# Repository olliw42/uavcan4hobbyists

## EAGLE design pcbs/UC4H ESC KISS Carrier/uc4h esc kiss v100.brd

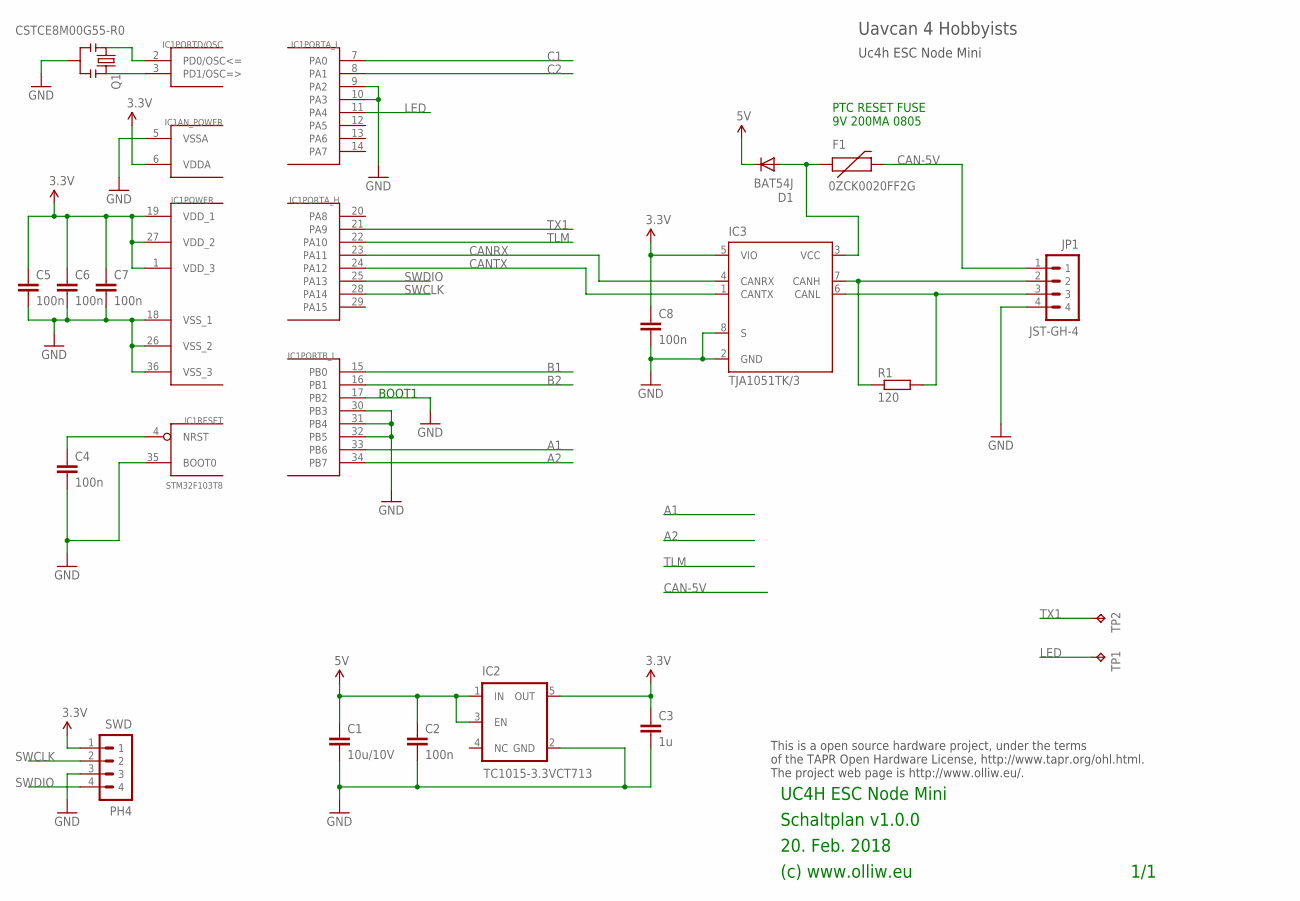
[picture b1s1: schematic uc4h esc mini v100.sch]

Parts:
C1: 10u/10V; C1206
C2, C4, C5, C6, C7, C8: 100n; C0603K
C3: 1u; C0603K
D1: BAT54J; SOD110-R
F1: 0ZCK0020FF2G; FUSE-0805
IC1: STM32F103T8; VFQFPN36
IC2: TC1015-3.3VCT713; SOT23-5
IC3: TJA1051TK/3; HVSON8
JP1: JST-GH-4; SM04B-GHS-TB
Q1: CSTCE8M00G55-R0; RESONATOR-SMD
R1: 120; R0603
SWD: PH4; 4X1_1P27_OCT_BILEX
TP1, TP2: TPB1,27; B1,27

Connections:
3.3V: C3.1, C5.1, C6.1, C7.1, C8.1, IC1.1 (VDD_3), IC1.6 (VDDA), IC1.19 (VDD_1), IC1.27 (VDD_2), IC2.5 (OUT), IC3.5 (VIO), SWD.1
5V: C1.1, C2.1, D1.C, IC2.1 (IN), IC2.3 (EN); also elsewhere on the board
A1: IC1.33 (PB6)
A2: IC1.34 (PB7)
B1: IC1.15 (PB0)
B2: IC1.16 (PB1)
C1: IC1.7 (PA0)
C2: IC1.8 (PA1)
CAN-5V: F1.2, JP1.1
CANH: IC3.7 (CANH), JP1.2, R1.1
CANL: IC3.6 (CANL), JP1.3, R1.2
CANRX: IC1.23 (PA11), IC3.4 (CANRX)
CANTX: IC1.24 (PA12), IC3.1 (CANTX)
GND: C1.2, C2.2, C3.2, C4.2, C5.2, C6.2, C7.2, C8.2, IC1.5 (VSSA), IC1.9 (PA2), IC1.10 (PA3), IC1.17 (PB2), IC1.18 (VSS_1), IC1.26 (VSS_2), IC1.30 (PB3), IC1.31 (PB4), IC1.32 (PB5), IC1.35 (BOOT0), IC1.36 (VSS_3), IC2.2 (GND), IC3.2 (GND), IC3.8 (S), JP1.4, Q1.2, SWD.3
LED: IC1.11 (PA4), TP1.TP
unnamed: C4.1, IC1.4 (NRST)
unnamed: D1.A, F1.1, IC3.3 (VCC)
unnamed: IC1.2 (PD0/OSC<=), Q1.1
unnamed: IC1.3 (PD1/OSC=>), Q1.3
SWCLK: IC1.28 (PA14), SWD.2
SWDIO: IC1.25 (PA13), SWD.4
TLM: IC1.22 (PA10)
TX1: IC1.21 (PA9), TP2.TP

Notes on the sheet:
20. Feb. 2018
(c) www.olliw.eu
UC4H ESC Node Mini
Schaltplan v1.0.0
This is a open source hardware project, under the terms of the TAPR Open Hardware License, http://www.tapr.org/ohl.html. The project web page is http://www.olliw.eu/.
1/1
Uc4h ESC Node Mini
Uavcan 4 Hobbyists
BOOT1
PTC RESET FUSE 9V 200MA 0805

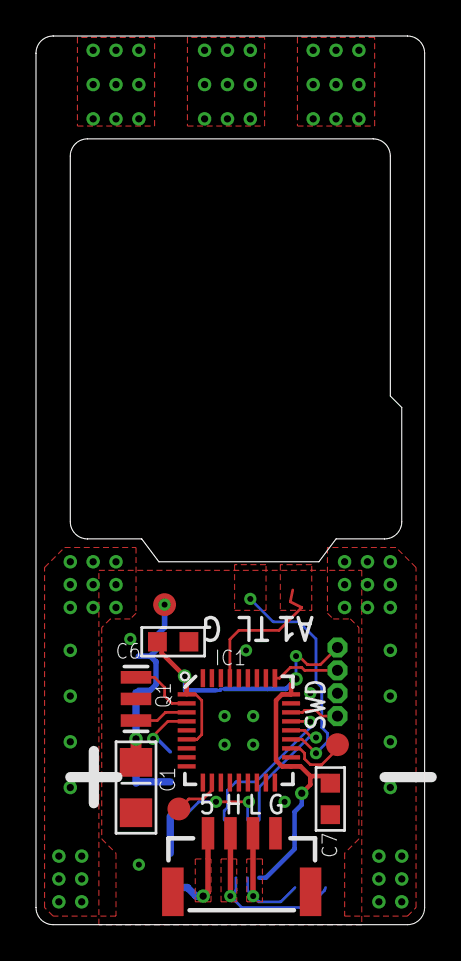
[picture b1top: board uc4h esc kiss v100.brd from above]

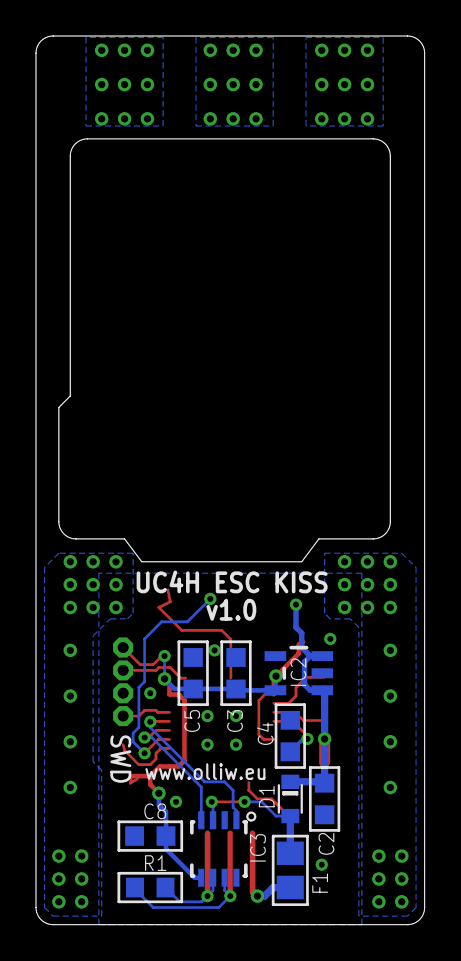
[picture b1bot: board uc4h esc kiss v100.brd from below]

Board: 2 copper layers, 21.6 x 49.4 mm, 20 parts (10 on the bottom side), 16 nets.

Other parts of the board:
TP3: TPB1,27; B1,27

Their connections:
5V: TP3.TP; also elsewhere on the board

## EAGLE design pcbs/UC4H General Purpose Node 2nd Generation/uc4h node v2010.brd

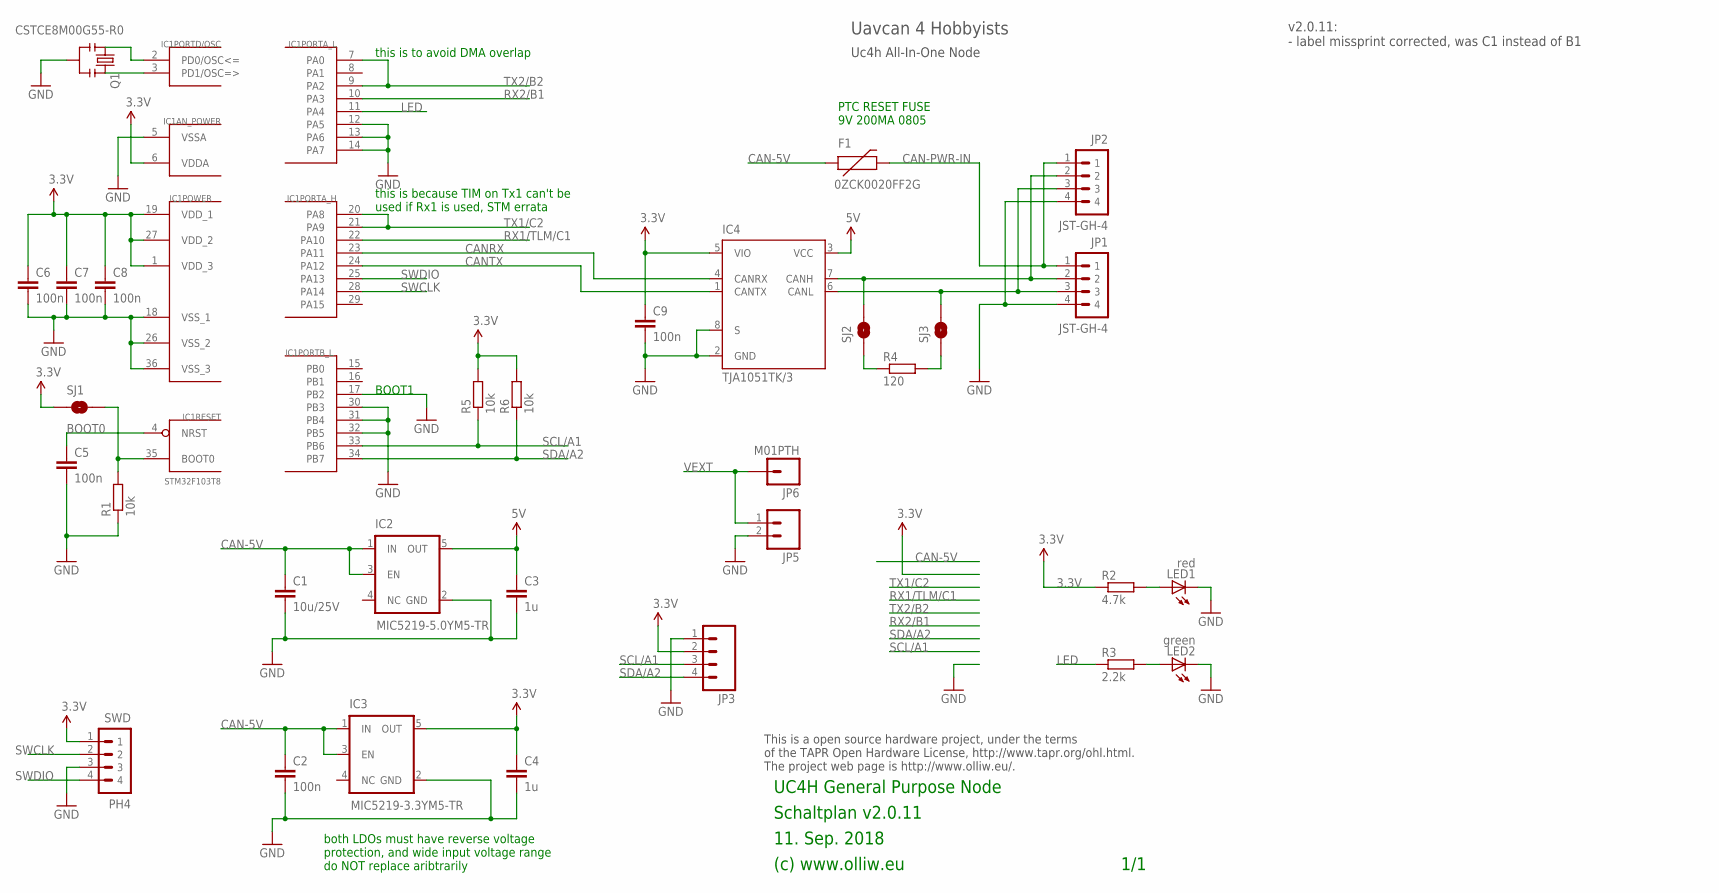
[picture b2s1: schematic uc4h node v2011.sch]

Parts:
C1: 10u/25V; C1206
C2, C5, C6, C7, C8, C9: 100n; C0603K
C3, C4: 1u; C0603K
F1: 0ZCK0020FF2G; FUSE-0805
IC1: STM32F103T8; VFQFPN36
IC2: MIC5219-5.0YM5-TR; SOT23-5
IC3: MIC5219-3.3YM5-TR; SOT23-5
IC4: TJA1051TK/3; HVSON8
JP1, JP2: JST-GH-4; SM04B-GHS-TB
JP3: M04PTH; 1X04
JP5: M02PTH; 1X02
JP6: M01PTH; 1X01
LED1: red; CHIPLED_0603
LED2: green; CHIPLED_0603
Q1: CSTCE8M00G55-R0; RESONATOR-SMD
R1, R5, R6: 10k; R0603
R2: 4.7k; R0603
R3: 2.2k; R0603
R4: 120; R0603
SJ1: BOOT0; SJ_2S-NO
SJ2, SJ3: SOLDERJUMPERNO; SJ_2S-NO
SWD: PH4; 4X1_1P27_OCT_BILEX

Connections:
3.3V: C4.1, C6.1, C7.1, C8.1, C9.1, IC1.1 (VDD_3), IC1.6 (VDDA), IC1.19 (VDD_1), IC1.27 (VDD_2), IC3.5 (OUT), IC4.5 (VIO), JP3.2, R2.1, R5.2, R6.2, SJ1.1, SWD.1
5V: C3.1, IC2.5 (OUT), IC4.3 (VCC)
CAN-5V: C1.1, C2.1, F1.1, IC2.1 (IN), IC2.3 (EN), IC3.1 (IN), IC3.3 (EN)
CAN-PWR-IN: F1.2, JP1.1, JP2.1
CANH: IC4.7 (CANH), JP1.2, JP2.2, SJ2.2
CANL: IC4.6 (CANL), JP1.3, JP2.3, SJ3.2
CANRX: IC1.23 (PA11), IC4.4 (CANRX)
CANTX: IC1.24 (PA12), IC4.1 (CANTX)
GND: C1.2, C2.2, C3.2, C4.2, C5.2, C6.2, C7.2, C8.2, C9.2, IC1.5 (VSSA), IC1.12 (PA5), IC1.13 (PA6), IC1.14 (PA7), IC1.17 (PB2), IC1.18 (VSS_1), IC1.26 (VSS_2), IC1.30 (PB3), IC1.31 (PB4), IC1.32 (PB5), IC1.36 (VSS_3), IC2.2 (GND), IC3.2 (GND), IC4.2 (GND), IC4.8 (S), JP1.4, JP2.4, JP3.1, JP5.2, LED1.C, LED2.C, Q1.2, R1.1, SWD.3
LED: IC1.11 (PA4), R3.1
unnamed: C5.1, IC1.4 (NRST)
unnamed: LED2.A, R3.2
unnamed: R4.1, SJ2.1
unnamed: IC1.2 (PD0/OSC<=), Q1.1
unnamed: IC1.3 (PD1/OSC=>), Q1.3
unnamed: R4.2, SJ3.1
unnamed: IC1.35 (BOOT0), R1.2, SJ1.2
unnamed: LED1.A, R2.2
RX1/TLM/C1: IC1.22 (PA10)
RX2/B1: IC1.10 (PA3)
SWCLK: IC1.28 (PA14), SWD.2
SWDIO: IC1.25 (PA13), SWD.4
TX1/C2: IC1.20 (PA8), IC1.21 (PA9)
TX2/B2: IC1.7 (PA0), IC1.9 (PA2)
VEXT: JP5.1, JP6.1

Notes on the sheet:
11. Sep. 2018
(c) www.olliw.eu
UC4H General Purpose Node
Schaltplan v2.0.11
This is a open source hardware project, under the terms of the TAPR Open Hardware License, http://www.tapr.org/ohl.html. The project web page is http://www.olliw.eu/.
1/1
Uc4h All-In-One Node
Uavcan 4 Hobbyists
BOOT1
PTC RESET FUSE 9V 200MA 0805
both LDOs must have reverse voltage protection, and wide input voltage range do NOT replace aribtrarily
this is to avoid DMA overlap
this is because TIM on Tx1 can't be used if Rx1 is used, STM errata
v2.0.11: - label missprint corrected, was C1 instead of B1

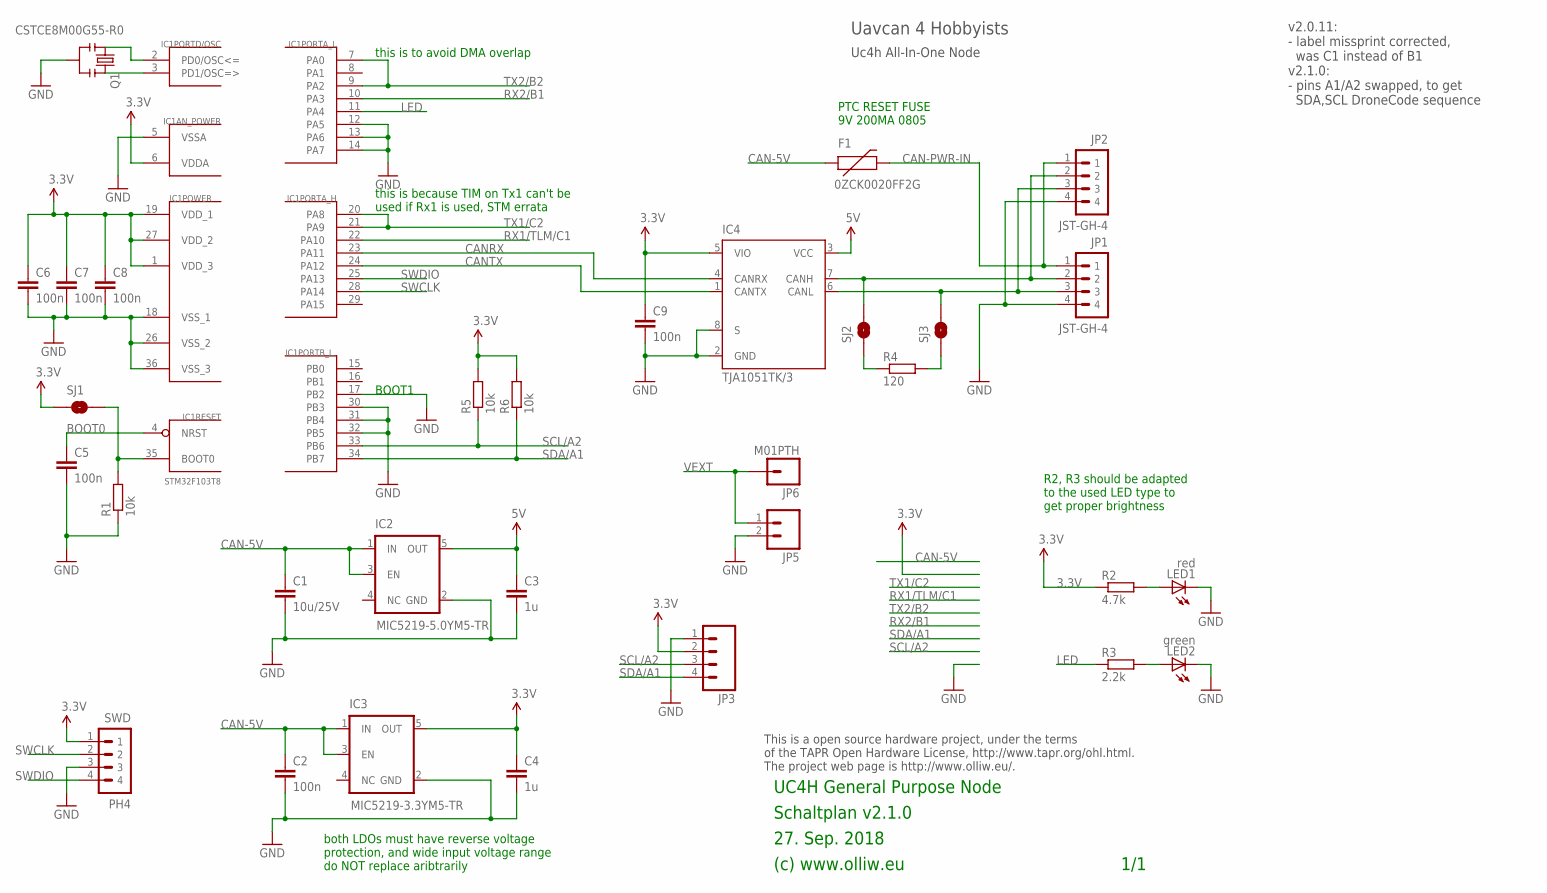
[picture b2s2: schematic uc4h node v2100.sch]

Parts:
C1: 10u/25V; C1206
C2, C5, C6, C7, C8, C9: 100n; C0603K
C3, C4: 1u; C0603K
F1: 0ZCK0020FF2G; FUSE-0805
IC1: STM32F103T8; VFQFPN36
IC2: MIC5219-5.0YM5-TR; SOT23-5
IC3: MIC5219-3.3YM5-TR; SOT23-5
IC4: TJA1051TK/3; HVSON8
JP1, JP2: JST-GH-4; SM04B-GHS-TB
JP3: M04PTH; 1X04
JP5: M02PTH; 1X02
JP6: M01PTH; 1X01
LED1: red; CHIPLED_0603
LED2: green; CHIPLED_0603
Q1: CSTCE8M00G55-R0; RESONATOR-SMD
R1, R5, R6: 10k; R0603
R2: 4.7k; R0603
R3: 2.2k; R0603
R4: 120; R0603
SJ1: BOOT0; SJ_2S-NO
SJ2, SJ3: SOLDERJUMPERNO; SJ_2S-NO
SWD: PH4; 4X1_1P27_OCT_BILEX

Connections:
3.3V: C4.1, C6.1, C7.1, C8.1, C9.1, IC1.1 (VDD_3), IC1.6 (VDDA), IC1.19 (VDD_1), IC1.27 (VDD_2), IC3.5 (OUT), IC4.5 (VIO), JP3.2, R2.1, R5.2, R6.2, SJ1.1, SWD.1
5V: C3.1, IC2.5 (OUT), IC4.3 (VCC)
CAN-5V: C1.1, C2.1, F1.1, IC2.1 (IN), IC2.3 (EN), IC3.1 (IN), IC3.3 (EN)
CAN-PWR-IN: F1.2, JP1.1, JP2.1
CANH: IC4.7 (CANH), JP1.2, JP2.2, SJ2.2
CANL: IC4.6 (CANL), JP1.3, JP2.3, SJ3.2
CANRX: IC1.23 (PA11), IC4.4 (CANRX)
CANTX: IC1.24 (PA12), IC4.1 (CANTX)
GND: C1.2, C2.2, C3.2, C4.2, C5.2, C6.2, C7.2, C8.2, C9.2, IC1.5 (VSSA), IC1.12 (PA5), IC1.13 (PA6), IC1.14 (PA7), IC1.17 (PB2), IC1.18 (VSS_1), IC1.26 (VSS_2), IC1.30 (PB3), IC1.31 (PB4), IC1.32 (PB5), IC1.36 (VSS_3), IC2.2 (GND), IC3.2 (GND), IC4.2 (GND), IC4.8 (S), JP1.4, JP2.4, JP3.1, JP5.2, LED1.C, LED2.C, Q1.2, R1.1, SWD.3
LED: IC1.11 (PA4), R3.1
unnamed: C5.1, IC1.4 (NRST)
unnamed: LED2.A, R3.2
unnamed: R4.1, SJ2.1
unnamed: IC1.2 (PD0/OSC<=), Q1.1
unnamed: IC1.3 (PD1/OSC=>), Q1.3
unnamed: R4.2, SJ3.1
unnamed: IC1.35 (BOOT0), R1.2, SJ1.2
unnamed: LED1.A, R2.2
RX1/TLM/C1: IC1.22 (PA10)
RX2/B1: IC1.10 (PA3)
SWCLK: IC1.28 (PA14), SWD.2
SWDIO: IC1.25 (PA13), SWD.4
TX1/C2: IC1.20 (PA8), IC1.21 (PA9)
TX2/B2: IC1.7 (PA0), IC1.9 (PA2)
VEXT: JP5.1, JP6.1

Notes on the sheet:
27. Sep. 2018
(c) www.olliw.eu
UC4H General Purpose Node
Schaltplan v2.1.0
This is a open source hardware project, under the terms of the TAPR Open Hardware License, http://www.tapr.org/ohl.html. The project web page is http://www.olliw.eu/.
1/1
Uc4h All-In-One Node
Uavcan 4 Hobbyists
BOOT1
PTC RESET FUSE 9V 200MA 0805
both LDOs must have reverse voltage protection, and wide input voltage range do NOT replace aribtrarily
this is to avoid DMA overlap
this is because TIM on Tx1 can't be used if Rx1 is used, STM errata
v2.0.11: - label missprint corrected, was C1 instead of B1 v2.1.0: - pins A1/A2 swapped, to get SDA,SCL DroneCode sequence
R2, R3 should be adapted to the used LED type to get proper brightness

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
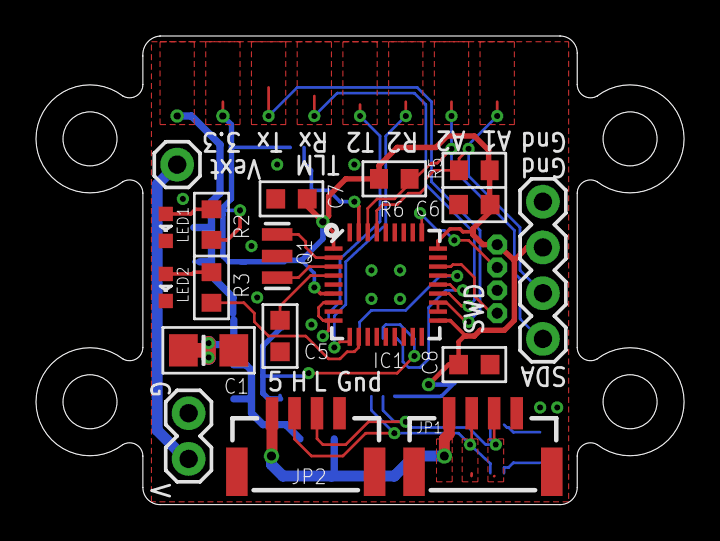
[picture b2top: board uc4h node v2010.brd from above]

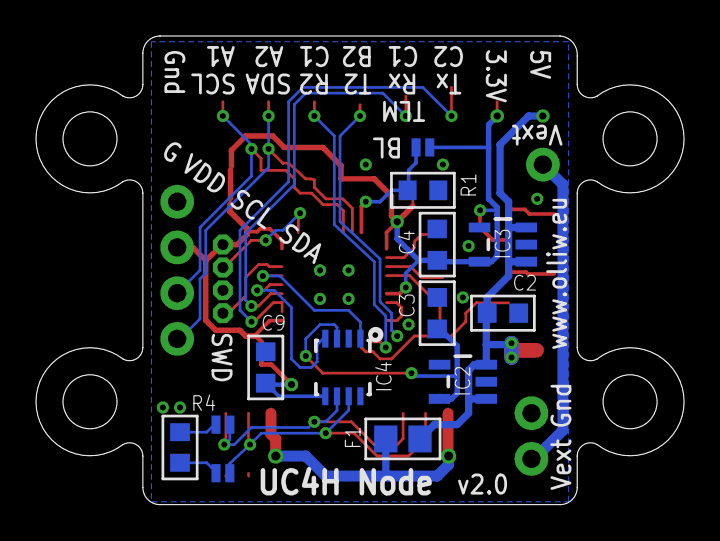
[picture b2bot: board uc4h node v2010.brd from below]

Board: 2 copper layers, 36.0 x 26.0 mm, 32 parts (13 on the bottom side), 25 nets.

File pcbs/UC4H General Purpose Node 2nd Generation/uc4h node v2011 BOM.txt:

Stückliste exportiert aus C:/Users/Olli/Documents/Elektronik/Eagle/Uavcan4Hobby/uc4h node v2010.sch am 02.08.2018 07:51

Part Value             Device                Package            Description                  
C1   10u/25V           C-EUC1206             C1206              CAPACITOR, European symbol   
C2   100n              C-EUC0603K            C0603K             CAPACITOR, European symbol   
C3   1u                C-EUC0603K            C0603K             CAPACITOR, European symbol   
C4   1u                C-EUC0603K            C0603K             CAPACITOR, European symbol   
C5   100n              C-EUC0603K            C0603K             CAPACITOR, European symbol   
C6   100n              C-EUC0603K            C0603K             CAPACITOR, European symbol   
C7   100n              C-EUC0603K            C0603K             CAPACITOR, European symbol   
C8   100n              C-EUC0603K            C0603K             CAPACITOR, European symbol   
C9   100n              C-EUC0603K            C0603K             CAPACITOR, European symbol   
F1   0ZCK0020FF2G      FUSE-PTCFUSE-0805     FUSE-0805                                       
IC1  STM32F103T8       STM32F10XTXU6         VFQFPN36           STM32F101/103 36pad VFQPFN36 
IC2  MIC5219-5.0YM5-TR V_REG_TPS76433SOT23-5 SOT23-5            Voltage Regulator            
IC3  MIC5219-3.3YM5-TR V_REG_TPS76433SOT23-5 SOT23-5            Voltage Regulator            
IC4  TJA1051TK/3       TJA1051TK/3           HVSON8                                          
JP1  JST-GH-4          JST-GH-4              SM04B-GHS-TB                                    
JP2  JST-GH-4          JST-GH-4              SM04B-GHS-TB                                    
JP3                    M04PTH                1X04               Header 4                     
JP5                    M02PTH                1X02               Header 2                     
JP6  M01PTH            M01PTH                1X01               Header 1                     
LED1 red               LEDCHIPLED_0603       CHIPLED_0603       LED                          
LED2 green             LEDCHIPLED_0603       CHIPLED_0603       LED                          
Q1   CSTCE8M00G55-R0   RESONATORSMD          RESONATOR-SMD      Resonator                    
R1   10k               R-EU_R0603            R0603              RESISTOR, European symbol    
R2   4.7k              R-EU_R0603            R0603              RESISTOR, European symbol    
R3   2.2k              R-EU_R0603            R0603              RESISTOR, European symbol    
R4   120               R-EU_R0603            R0603              RESISTOR, European symbol    
R5   10k               R-EU_R0603            R0603              RESISTOR, European symbol    
R6   10k               R-EU_R0603            R0603              RESISTOR, European symbol    
SJ1  BOOT0             SOLDERJUMPERNO        SJ_2S-NO           Solder Jumper                
SJ2                    SOLDERJUMPERNO        SJ_2S-NO           Solder Jumper                
SJ3                    SOLDERJUMPERNO        SJ_2S-NO           Solder Jumper                
SWD  PH4               P4X1_1P27-OCT_BILEX   4X1_1P27_OCT_BILEX

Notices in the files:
parts and their libraries:
Licensing: CC v3.0 Share-Alike You are welcome to use this library for commercial purposes.
